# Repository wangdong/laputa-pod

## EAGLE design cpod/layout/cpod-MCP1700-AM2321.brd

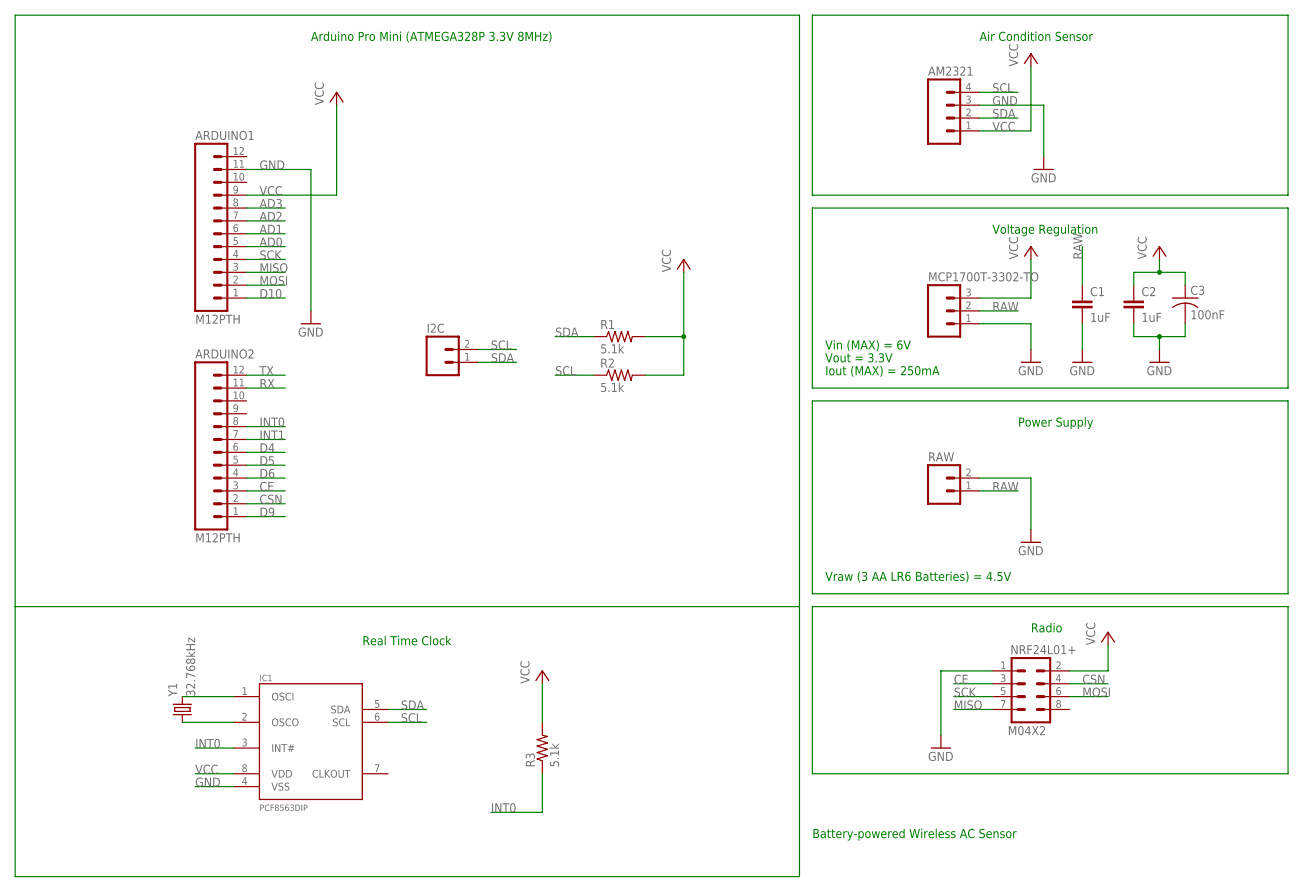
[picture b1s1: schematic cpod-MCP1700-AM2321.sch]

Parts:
AM2321: M04PTH; 1X04
ARDUINO1, ARDUINO2: M12PTH; 1X12
C1, C2: 1uF; CAP-PTH-SMALL
C3: 100nF; C025-024X044
I2C: M02PTH; 1X02
IC1: PCF8563DIP; DIL08
MCP1700T-3302-TO: M03PTH; 1X03
NRF24L01+: M04X2; 2X4
R1, R2: 5.1k; 0207/2V
R3: 5.1k; 0204/7
RAW: M02PTH; 1X02
Y1: 32.768kHz; TC26H

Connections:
AD0: ARDUINO1.5
AD1: ARDUINO1.6
AD2: ARDUINO1.7
AD3: ARDUINO1.8
CE: ARDUINO2.3, NRF24L01+.3
CSN: ARDUINO2.2, NRF24L01+.4
D4: ARDUINO2.6
D5: ARDUINO2.5
D6: ARDUINO2.4
D9: ARDUINO2.1
D10: ARDUINO1.1
GND: AM2321.3, ARDUINO1.11, C1.2, C2.2, C3.2, IC1.4 (VSS), MCP1700T-3302-TO.1, NRF24L01+.1, RAW.2
INT0: ARDUINO2.8, IC1.3 (INT#), R3.1
INT1: ARDUINO2.7
MISO: ARDUINO1.3, NRF24L01+.7
MOSI: ARDUINO1.2, NRF24L01+.6
unnamed: IC1.1 (OSCI), Y1.2
unnamed: IC1.2 (OSCO), Y1.1
RAW: C1.1, MCP1700T-3302-TO.2, RAW.1
RX: ARDUINO2.11
SCK: ARDUINO1.4, NRF24L01+.5
SCL: AM2321.4, I2C.2, IC1.6 (SCL), R2.1
SDA: AM2321.2, I2C.1, IC1.5 (SDA), R1.1
TX: ARDUINO2.12
VCC: AM2321.1, ARDUINO1.9, C2.1, C3.1, IC1.8 (VDD), MCP1700T-3302-TO.3, NRF24L01+.2, R1.2, R2.2, R3.2

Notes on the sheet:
Vin (MAX) = 6V
Iout (MAX) = 250mA
Voltage Regulation
Air Condition Sensor
Power Supply
Radio
Arduino Pro Mini (ATMEGA328P 3.3V 8MHz)
Battery-powered Wireless AC Sensor
Vraw (3 AA LR6 Batteries) = 4.5V
Vout = 3.3V
Real Time Clock

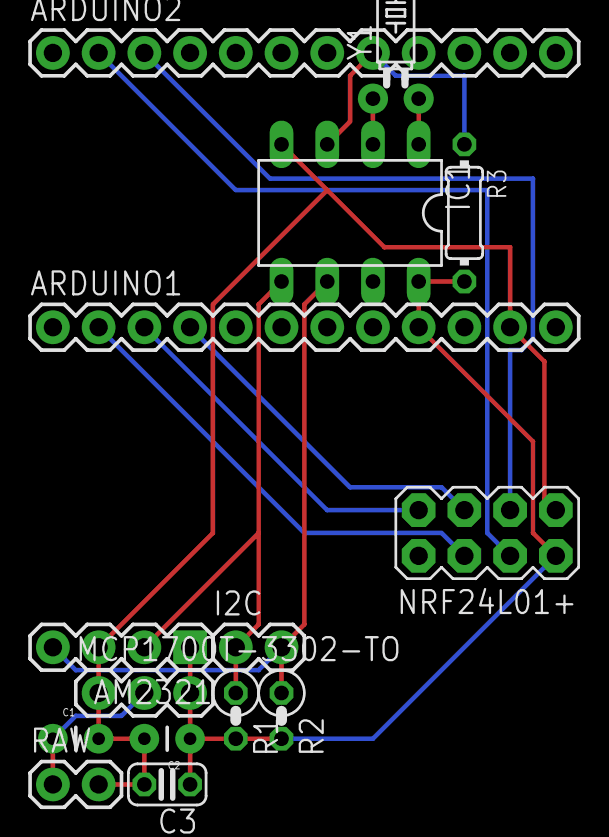
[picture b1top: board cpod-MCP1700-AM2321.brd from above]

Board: 2 copper layers, 16 parts (0 on the bottom side), 13 nets.

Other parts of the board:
U$2: OSHW-LOGO-L

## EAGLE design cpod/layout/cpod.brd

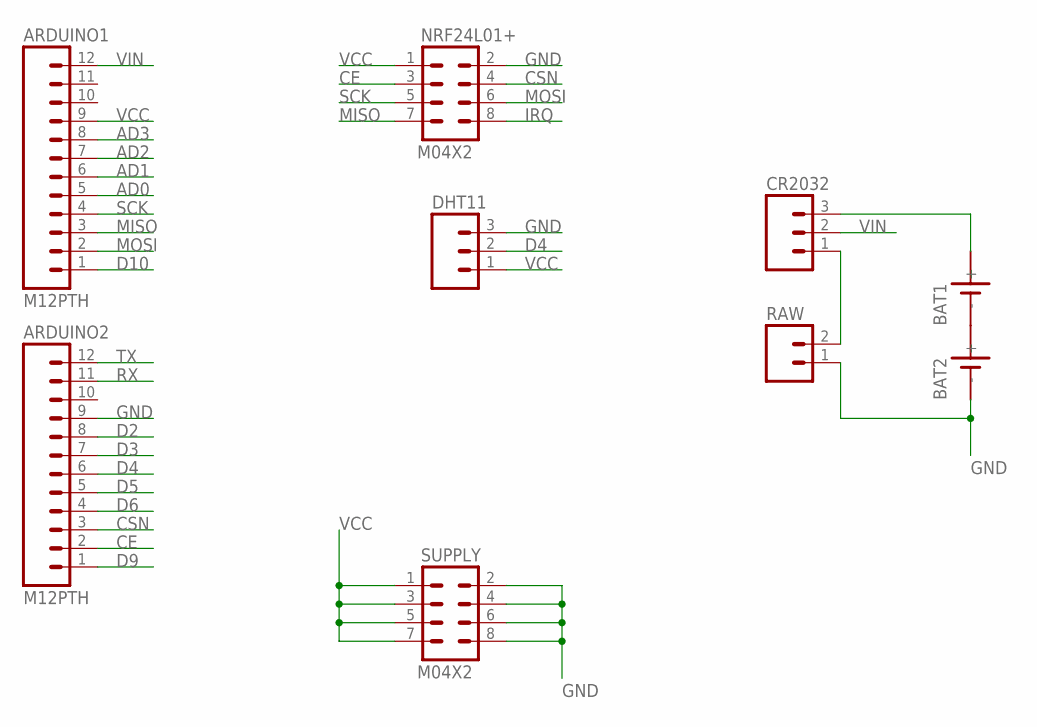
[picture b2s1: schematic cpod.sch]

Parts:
ARDUINO1, ARDUINO2: M12PTH; 1X12
BAT1, BAT2: SN2032
CR2032: M03PTH; 1X03
DHT11: M03PTH; 1X03
NRF24L01+: M04X2; 2X4
RAW: M02PTH; 1X02
SUPPLY: M04X2; 2X4

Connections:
AD0: ARDUINO1.5
AD1: ARDUINO1.6
AD2: ARDUINO1.7
AD3: ARDUINO1.8
CE: ARDUINO2.2, NRF24L01+.3
CSN: ARDUINO2.3, NRF24L01+.4
D2: ARDUINO2.8
D3: ARDUINO2.7
D4: ARDUINO2.6, DHT11.2
D5: ARDUINO2.5
D6: ARDUINO2.4
D9: ARDUINO2.1
D10: ARDUINO1.1
GND: ARDUINO2.9, BAT2.-, DHT11.3, NRF24L01+.2, RAW.1, SUPPLY.2, SUPPLY.4, SUPPLY.6, SUPPLY.8
IRQ: NRF24L01+.8
MISO: ARDUINO1.3, NRF24L01+.7
MOSI: ARDUINO1.2, NRF24L01+.6
unnamed: BAT1.-, BAT2.+
unnamed: BAT1.+, CR2032.3
unnamed: CR2032.1, RAW.2
RX: ARDUINO2.11
SCK: ARDUINO1.4, NRF24L01+.5
TX: ARDUINO2.12
VCC: ARDUINO1.9, DHT11.1, NRF24L01+.1, SUPPLY.1, SUPPLY.3, SUPPLY.5, SUPPLY.7
VIN: ARDUINO1.12, CR2032.2

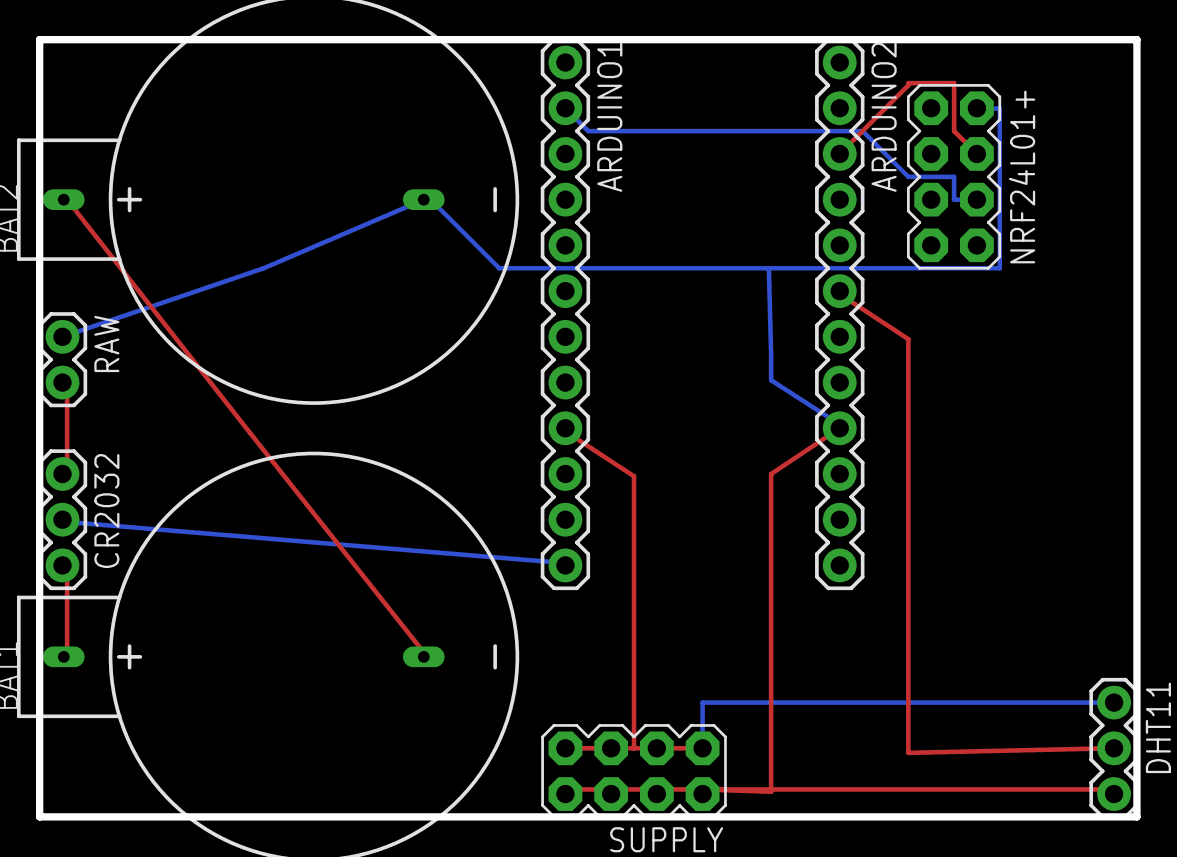
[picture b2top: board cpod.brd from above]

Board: 2 copper layers, 61.0 x 43.2 mm, 9 parts (0 on the bottom side), 12 nets.

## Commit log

2013-04-24 init
2013-04-24 完全可以正常接收传感器数据
2013-04-24 超时机制完成，增加-d参数用来诊断
2013-04-24 完成了向cosm feed投递
2013-04-26 cpod入库
2013-04-26 删除可执行文件
2013-04-26 目录结构调整
2013-04-26 整理了配置
2013-04-26 char*=>const char*
2013-04-26 datagram完成
2013-04-26 服务端完成
2013-04-26 客户端修改完成
2013-04-26 feed脚本完成
2013-04-27 PCB布局完毕
2013-04-28 增加了对eagle文件的ignore
2013-04-28 增加新节点
2013-04-28 NRF24L01+下调一格
2013-04-30 低功耗完成
2013-05-01 布线完成
2013-05-01 可以说是比较完美的一个布局
2013-05-01 改为单总线
2013-05-02 留出了电解电容的位置
2013-05-03 换用独石电容
2013-05-03 增加了DS1302
2013-05-04 去掉了SUPPLY
2013-05-04 增加了去耦电容
2013-05-04 原理图错误mirror了，改过来
2013-05-04 I2C的上拉电阻改到5.1k
2013-05-04 把去耦放到电源框里，增加表意性。
2013-05-05 增加INT0的上拉电阻
2013-05-05 上拉电阻布线
2013-05-05 调整了PCB，变得更清晰一些
2013-05-06 增加sleep时间，降低CPU占用
2013-05-06 PCB定稿
2013-05-07 new lib
2013-05-07 恢复高CPU的模式
2013-05-07 每3分钟测量一次
2013-05-08 细微修正，周期改为2min
2013-05-08 done
2013-05-08 修正了没有powerDown的问题
2013-05-09 killall
2013-05-11 只有发送的瞬间才打开radio进一步渐少能耗
2013-05-11 改正语法错误
2013-05-14 改新接口
2013-05-14 改为xively
2013-05-14 改BUG
2013-05-18 降低速率
2013-05-19 daemon
2013-05-19 新的上报方式完成，可以支持多个传感器
2013-05-19 增加了syslog
2013-05-19 改用UTC
2013-05-19 改进提示
2013-05-23 通过看门狗每周重置一次
2013-06-24 fixed for rasbian
2014-05-26 RF24: 按照新的引脚规范定义nRF24
    * PIN24(CSN)-PIN16(CE)-PIN13(IRQ), 第一块nRF24
    * PIN26(CSN)-PIN18(CE)-PIN15(IRQ), 第二块nRF24
    * IRQ不一定连接了，要看实际电路，一般悬空
    * 注意，raspberry的官方文档称SPI的CSN为CE，PIN24与26被成为CE0与CE1，这样做是错误的，要注意纠正为CSN，否则会与nRF24的CE混淆。nRF24的CE有效是做收发
2014-05-26 rmsg: 还未成功
2014-05-26 更新.gitignore
2014-05-26 发送成功
2014-05-28 so文件不入库
2014-05-28 rmsg: 改掉为新的管道地址
2014-05-28 增加了地址参数
2014-05-28 不再关闭电源
2014-06-03 rmsg: 多项调整
    - 地址换用feedf00d
    - 增加了两个radio的config
    - 去掉了AutoAck
2014-06-03 rmsg: 完成,AutoAck是要再次listening
2014-06-03 rmsg: PALevel

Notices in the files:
parts and their libraries:
SparkFun-Connectors: Licensing: CC v3.0 Share-Alike You are welcome to use this library for commercial purposes.
